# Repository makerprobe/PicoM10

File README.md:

# PicoM10
A pretty small ublox MIA-M10Q based GNSS module

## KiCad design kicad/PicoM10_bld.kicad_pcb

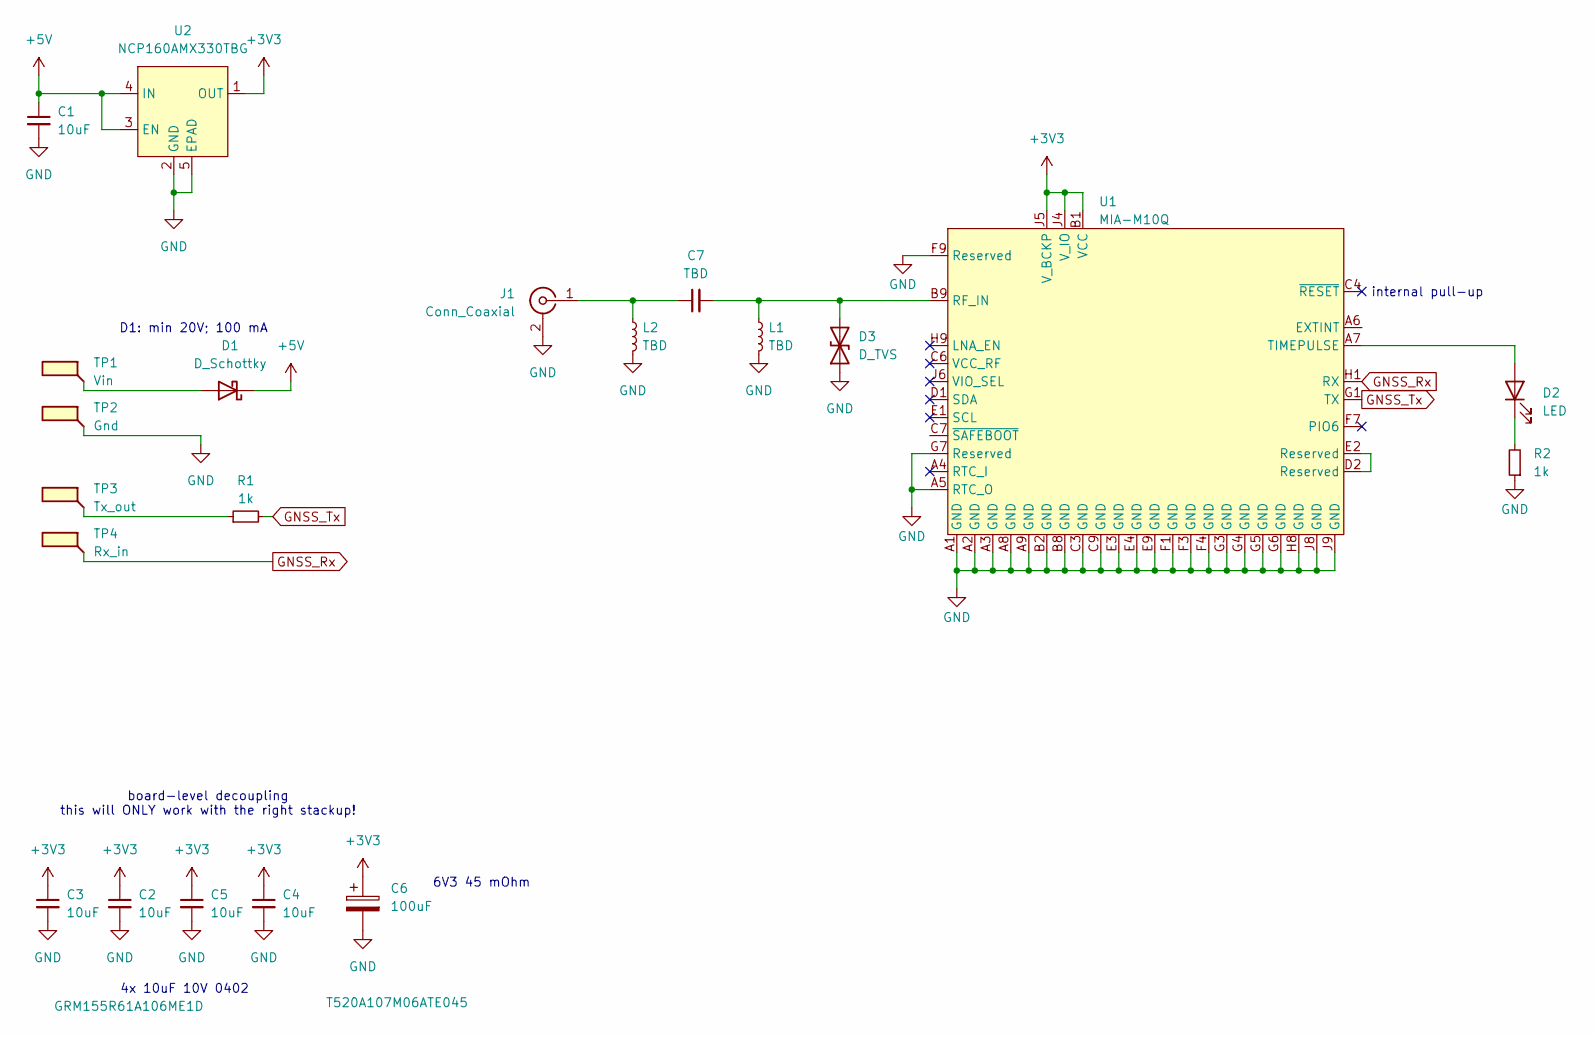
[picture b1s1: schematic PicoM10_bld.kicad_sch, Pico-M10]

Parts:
C1, C2, C3, C4, C5: 10uF; C_0402_1005Metric; MPN GRM155R61A106ME1D
C6: 100uF; CP_EIA-3216-10_Kemet-I; MPN T520A107M06ATE045
C7: TBD; C_0201_0603Metric_mod
D1: D_Schottky; D_SOD-923
D2: LED; LED_0201_0603Metric_mod
D3: D_TVS; Nexperia_DSN0603-2_0.6x0.3mm_P0.4mm
J1: Conn_Coaxial; U.FL_Molex_MCRF_73412-0110_Vertical; MPN CONMHF1-SMD-G-T
L1, L2: TBD; C_0201_0603Metric_mod
R1, R2: 1k; R_0201_0603Metric_mod
TP1: Vin; solderpad_castellated_2x2mm
TP2: Gnd; solderpad_castellated_2x2mm
TP3: Tx_out; solderpad_castellated_2x2mm
TP4: Rx_in; solderpad_castellated_2x2mm
U1: MIA-M10Q; SLGA-53_MIA-M10Q; MPN MIA-M10Q
U2: NCP160AMX330TBG; UDFN-4-1EP_1x1mm_P0.65mm_EP0.48x0.48mm; MPN NCP160AMX330TBG

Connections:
+3V3: C2.1, C3.1, C4.1, C5.1, C6.1, U1.B1 (VCC), U1.J4 (V_IO), U1.J5 (V_BCKP), U2.1 (OUT)
+5V: C1.1, D1.1 (K), U2.3 (EN), U2.4 (IN)
GND: C1.2, C2.2, C3.2, C4.2, C5.2, C6.2, D3.1 (A1), J1.2 (Ext), L1.2, L2.2, R2.1, TP2.1, U1.A1 (GND), U1.A2 (GND), U1.A3 (GND), U1.A5 (RTC_O), U1.A8 (GND), U1.A9 (GND), U1.B2 (GND), U1.B8 (GND), U1.C3 (GND), U1.C9 (GND), U1.E3 (GND), U1.E4 (GND), U1.E9 (GND), U1.F1 (GND), U1.F3 (GND), U1.F4 (GND), U1.F9 (Reserved), U1.G3 (GND), U1.G4 (GND), U1.G5 (GND), U1.G6 (GND), U1.G7 (Reserved), U1.H8 (GND), U1.J8 (GND), U1.J9 (GND), U2.2 (GND), U2.5 (EPAD)
GNSS_Rx: TP4.1, U1.H1 (RX)
GNSS_Tx: R1.2, U1.G1 (TX)
unnamed: D1.2 (A), TP1.1
unnamed: D2.2 (A), U1.A7 (TIMEPULSE)
unnamed: D2.1 (K), R2.2
unnamed: C7.2, D3.2 (A2), L1.1, U1.B9 (RF_IN)
unnamed: C7.1, J1.1 (In), L2.1
unnamed: R1.1, TP3.1
unnamed: U1.D2 (Reserved), U1.E2 (Reserved)

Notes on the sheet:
D1: min 20V; 100 mA
4x 10uF 10V 0402
board-level decoupling this will ONLY work with the right stackup!
internal pull-up
6V3 45 mOhm

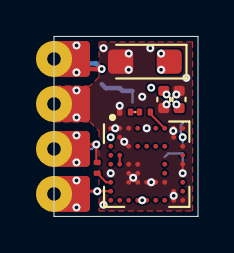
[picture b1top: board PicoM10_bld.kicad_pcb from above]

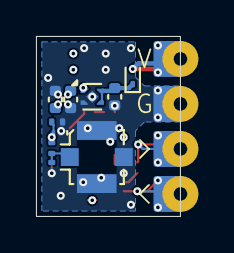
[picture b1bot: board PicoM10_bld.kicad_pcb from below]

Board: 6 copper layers, 8.0 x 10.0 mm, 21 parts (10 on the bottom side), 12 nets.

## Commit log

2024-11-04 initial kicad commit
2024-11-04 move to kicad folder
2024-11-04 minor cleanup and updates
2024-11-04 minor update
2024-11-04 documentation
2024-11-05 test
2024-11-05 minor schematic and layout updates
2024-11-05 M10 mask and paste, minor updates
2024-12-11 add TVS diode
